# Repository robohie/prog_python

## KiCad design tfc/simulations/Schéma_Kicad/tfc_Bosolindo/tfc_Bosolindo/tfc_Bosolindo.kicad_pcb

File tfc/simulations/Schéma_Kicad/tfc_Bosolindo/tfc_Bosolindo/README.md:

# Fichiers du projet KiCad

Ce dossier contient le projet KiCad `tfc_Bosolindo` : configuration du projet (`.kicad_pro`), schéma (`.kicad_sch`) et circuit imprimé (`.kicad_pcb`). Ouvrez le fichier de projet avec KiCad pour accéder à la conception complète.

Les fichiers auxiliaires d’état de l’éditeur peuvent être générés localement par KiCad.

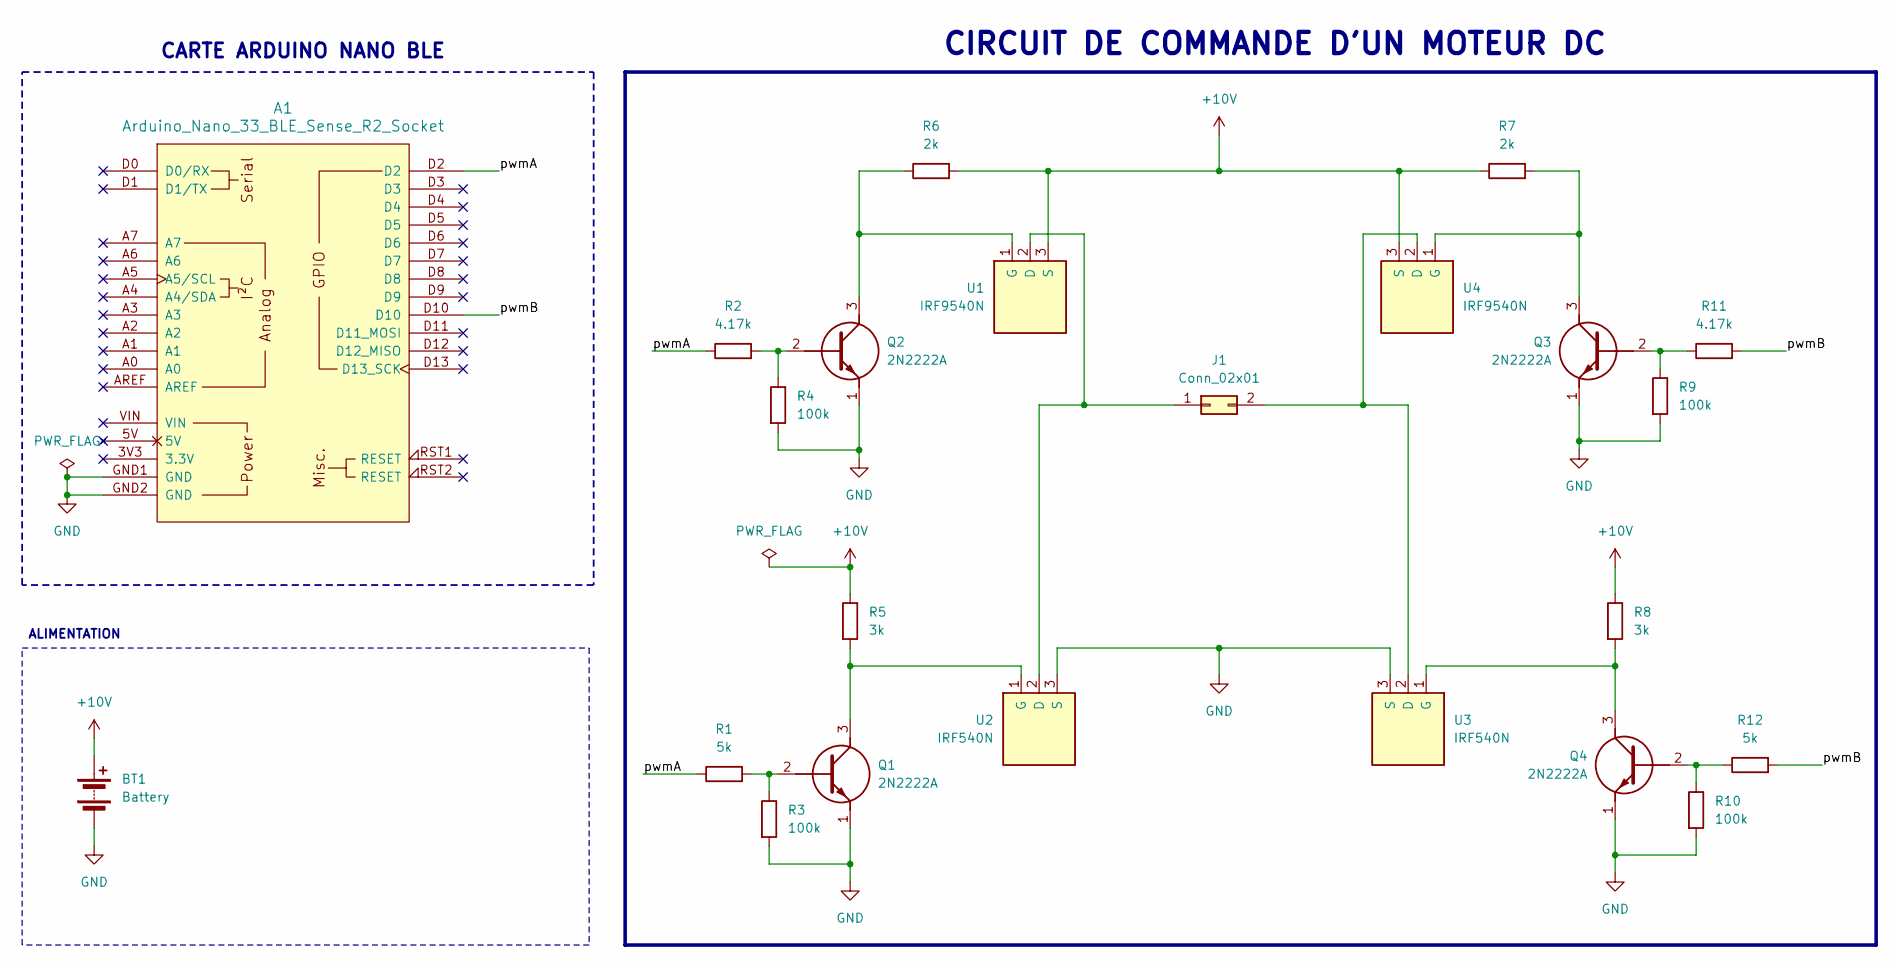
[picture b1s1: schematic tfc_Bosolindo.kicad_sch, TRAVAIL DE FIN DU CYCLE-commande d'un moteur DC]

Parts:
A1: Arduino_Nano_33_BLE_Sense_R2_Socket; Arduino_Nano_Every_Socket
BT1: Battery; PinHeader_2x01_P2.00mm_Vertical
J1: Conn_02x01; PinHeader_2x01_P2.00mm_Vertical
Q1, Q2, Q3, Q4: 2N2222A; Manufacturer_Part_Number 2N2222A; Mouser Part Number 494-2N2222A
R1, R12: 5k; R_Axial_DIN0309_L9.0mm_D3.2mm_P15.24mm_Horizontal
R2, R11: 4.17k; R_Axial_DIN0309_L9.0mm_D3.2mm_P15.24mm_Horizontal
R3, R4, R9, R10: 100k; R_Axial_DIN0309_L9.0mm_D3.2mm_P15.24mm_Horizontal
R5, R8: 3k; R_Axial_DIN0309_L9.0mm_D3.2mm_P15.24mm_Horizontal
R6, R7: 2k; R_Axial_DIN0309_L9.0mm_D3.2mm_P15.24mm_Horizontal
U1, U4: IRF9540N; TO-220-3_Vertical
U2, U3: IRF540N; TO-220-3_Vertical

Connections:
+10V: BT1.1 (+), R5.1, R6.2, R7.1, R8.1, U1.3 (S), U4.3 (S)
/pwmA: A1.D2, R1.1, R2.1
/pwmB: A1.D10, R11.2, R12.2
GND: A1.GND1 (GND), A1.GND2 (GND), BT1.2 (-), Q1.1 (E), Q2.1 (E), Q3.1 (E), Q4.1 (E), R3.2, R4.2, R9.2, R10.2, U2.3 (S), U3.3 (S)
unnamed: J1.1, U1.2 (D), U2.2 (D)
unnamed: J1.2, U3.2 (D), U4.2 (D)
unnamed: Q1.2 (B), R1.2, R3.1
unnamed: Q1.3 (C), R5.2, U2.1 (G)
unnamed: Q2.2 (B), R2.2, R4.1
unnamed: Q2.3 (C), R6.1, U1.1 (G)
unnamed: Q3.2 (B), R9.1, R11.1
unnamed: Q3.3 (C), R7.2, U4.1 (G)
unnamed: Q4.2 (B), R10.1, R12.1
unnamed: Q4.3 (C), R8.2, U3.1 (G)

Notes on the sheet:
CIRCUIT DE COMMANDE D'UN MOTEUR DC
CARTE ARDUINO NANO BLE
ALIMENTATION

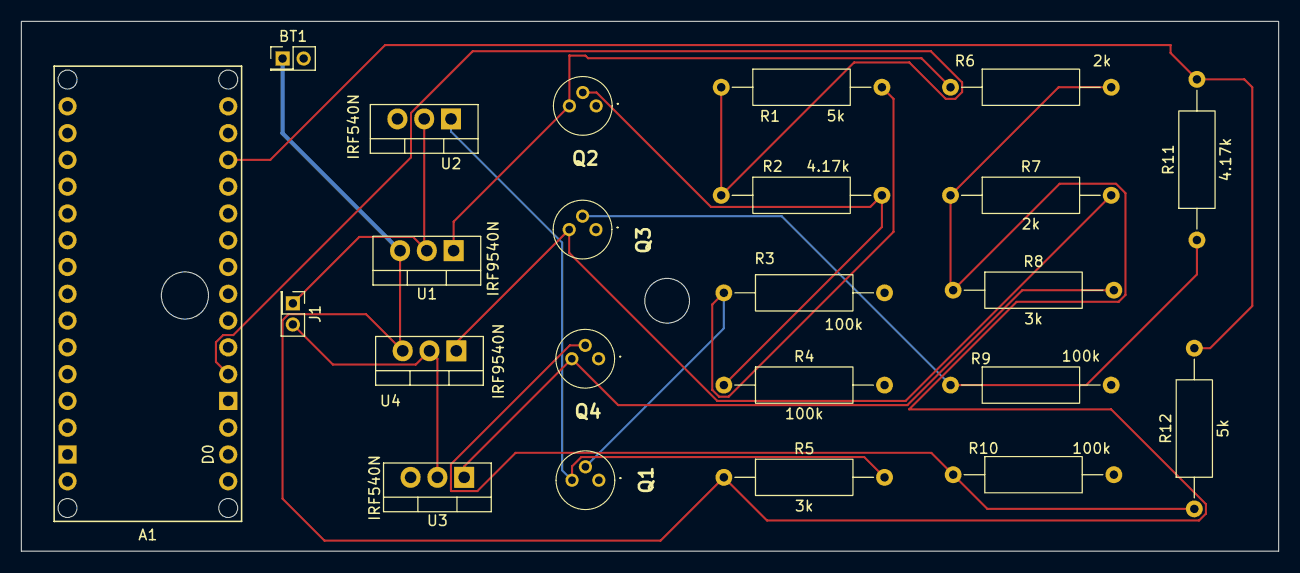
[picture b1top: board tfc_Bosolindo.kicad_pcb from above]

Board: 2 copper layers, 119.2 x 50.2 mm, 23 parts (0 on the bottom side), 14 nets.
